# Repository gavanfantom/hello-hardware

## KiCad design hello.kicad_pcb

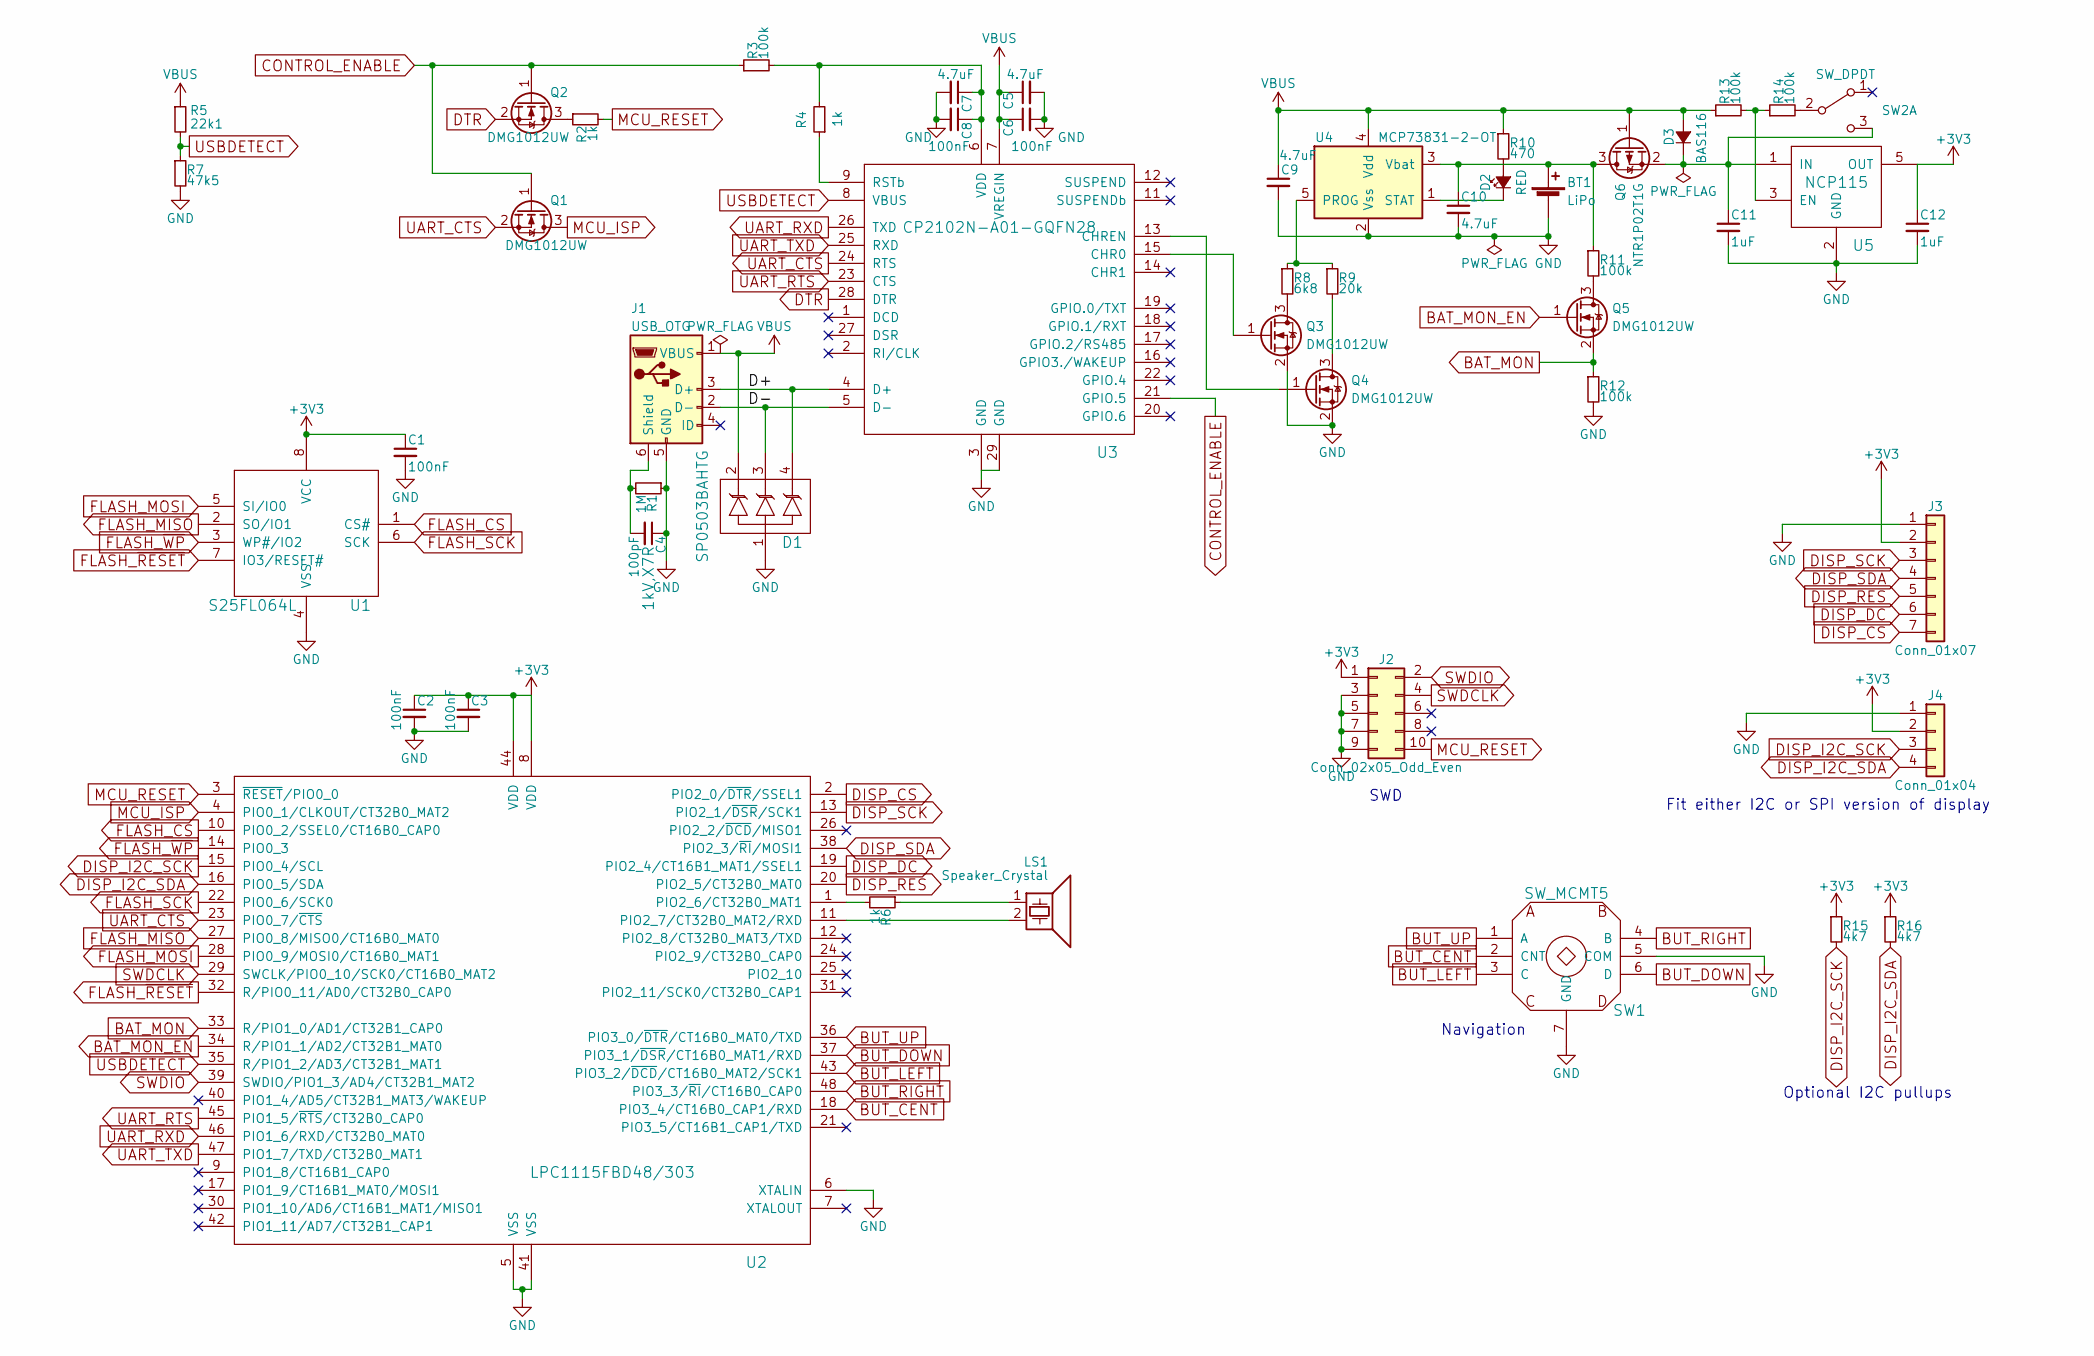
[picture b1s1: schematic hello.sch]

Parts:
BT1: LiPo; JST_PH_S2B-PH-SM4-TB_02x2.00mm_Angled; MPN S2B-PH-SM4-TB(LF)(SN)
C1, C2, C3, C6, C8: 100nF; C_0402; MPN MC0402B104K160CT
C4: 100pF; C_0805; MPN 885342207015
C5, C7, C9, C10: 4.7uF; C_0402; MPN AMK105BJ475MV-F
C11, C12: 1uF; C_0402; MPN GRM155R61E105KA12D
D1: SP0503BAHTG; SOT-143; MPN SP0503BAHTG
D2: RED; LED_0603; MPN KPT-1608EC
D3: BAS116; SOT-23; MPN BAS116 RF
J1: USB_OTG; USB_Micro-B_10118193-0001LF; MPN 10118193-0001LF
J2: Conn_02x05_Odd_Even; Pin_Header_Straight_2x05_Pitch1.27mm
J3: Conn_01x07; Pin_Header_Straight_1x07_Pitch2.54mm
J4: Conn_01x04; Pin_Header_Straight_1x04_Pitch2.54mm
LS1: Speaker_Crystal; PKMCS0909E4000-R1; MPN PKMCS0909E4000-R1
Q1, Q2, Q3, Q4, Q5: DMG1012UW; SOT-323_SC-70; MPN DMG1012UW
Q6: NTR1P02T1G; SOT-23; MPN NTR1P02T1G
R1: 1M; R_0603; MPN MCWR06X1004FTL
R2, R4, R6: 1k; R_0402; MPN MCWR04X1001FTL
R3, R11, R12, R13, R14: 100k; R_0402; MPN ERJ2RKF1003X
R5: 22k1; R_0402; MPN MCWR04X2212FTL
R7: 47k5; R_0402; MPN MCWR04X4752FTL
R8: 6k8; R_0402; MPN MCWR04X6801FTL
R9: 20k; R_0402; MPN MCWR04X2002FTL
R10: 470; R_0402; MPN MCWR04X4700FTL
R15, R16: 4k7; R_0402; MPN MCWR04X4701FTL
SW1: SW_MCMT5; Multicomp_MCMT5; MPN MCMT5-F-V
SW2: SW_DPDT; CK_JS202011SCQN; MPN JS202011SCQN
U1: S25FL064L; SOIJ-8_5.3x5.3mm_Pitch1.27mm; MPN S25FL064LABMFI010
U2: LPC1115FBD48/303; LQFP-48_7x7mm_Pitch0.5mm; MPN LPC1115FBD48/303
U3: CP2102N-A01-GQFN28; QFN-28-1EP_5x5mm_Pitch0.5mm; MPN CP2102N-A01-GQFN28
U4: MCP73831-2-OT; SOT-23-5; MPN MCP73831T-2ACI/OT
U5: NCP115; TSOP-5; MPN NCP115ASN330T2G

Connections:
+3V3: C1.1, C2.1, C3.1, C12.1, J2.1, J3.2, J4.2, R15.1, R16.1, U1.8 (VCC), U2.8 (VDD), U2.44 (VDD), U5.5 (OUT)
/D+: D1.4, J1.3 (D+), U3.4 (D+)
/D-: D1.3, J1.2 (D-), U3.5 (D-)
BAT_MON: Q5.2 (S), R12.1, U2.33 (R/PIO1_0/AD1/CT32B1_CAP0)
BAT_MON_EN: Q5.1 (G), U2.34 (R/PIO1_1/AD2/CT32B1_MAT0)
BUT_CENT: SW1.2 (CNT), U2.18 (PIO3_4/CT16B0_CAP1/RXD)
BUT_DOWN: SW1.6 (D), U2.37 (PIO3_1/~DSR~/CT16B0_MAT1/RXD)
BUT_LEFT: SW1.3 (C), U2.43 (PIO3_2/~DCD~/CT16B0_MAT2/SCK1)
BUT_RIGHT: SW1.4 (B), U2.48 (PIO3_3/~RI~/CT16B0_CAP0)
BUT_UP: SW1.1 (A), U2.36 (PIO3_0/~DTR~/CT16B0_MAT0/TXD)
CONTROL_ENABLE: Q1.1 (G), Q2.1 (G), R3.1, U3.21 (GPIO.5)
DISP_CS: J3.7, U2.2 (PIO2_0/~DTR~/SSEL1)
DISP_DC: J3.6, U2.19 (PIO2_4/CT16B1_MAT1/SSEL1)
DISP_I2C_SCK: J4.3, R15.2, U2.15 (PIO0_4/SCL)
DISP_I2C_SDA: J4.4, R16.2, U2.16 (PIO0_5/SDA)
DISP_RES: J3.5, U2.20 (PIO2_5/CT32B0_MAT0)
DISP_SCK: J3.3, U2.13 (PIO2_1/~DSR~/SCK1)
DISP_SDA: J3.4, U2.38 (PIO2_3/~RI~/MOSI1)
DTR: Q2.2 (S), U3.28 (DTR)
FLASH_CS: U1.1 (CS#), U2.10 (PIO0_2/SSEL0/CT16B0_CAP0)
FLASH_MISO: U1.2 (SO/IO1), U2.27 (PIO0_8/MISO0/CT16B0_MAT0)
FLASH_MOSI: U1.5 (SI/IO0), U2.28 (PIO0_9/MOSI0/CT16B0_MAT1)
FLASH_SCK: U1.6 (SCK), U2.22 (PIO0_6/SCK0)
FLASH_~RESET~: U1.7 (IO3/RESET#), U2.32 (R/PIO0_11/AD0/CT32B0_CAP0)
FLASH_~WP~: U1.3 (WP#/IO2), U2.14 (PIO0_3)
GND: BT1.2 (-), C1.2, C2.2, C3.2, C4.1, C5.2, C6.2, C7.2, C8.2, C9.2, C10.2, C11.2, C12.2, D1.1, J1.5 (GND), J2.3, J2.5, J2.7, J2.9, J3.1, J4.1, Q3.2 (S), Q4.2 (S), R1.1, R7.2, R12.2, SW1.5 (COM), SW1.7 (GND), U1.4 (VSS), U2.5 (VSS), U2.6 (XTALIN), U2.41 (VSS), U3.3 (GND), U3.29 (GND), U4.2 (Vss), U5.2 (GND)
MCU_ISP: Q1.3 (D), U2.4 (PIO0_1/CLKOUT/CT32B0_MAT2)
MCU_RESET: J2.10, R2.2, U2.3 (~RESET~/PIO0_0)
unnamed: BT1.1 (+), C10.1, Q6.3 (D), R11.1, U4.3 (Vbat)
unnamed: C4.2, J1.6 (Shield), R1.2
unnamed: C7.1, C8.1, R3.2, R4.2, U3.6 (VDD)
unnamed: C11.1, D3.3 (K), Q6.2 (S), SW2.3 (C), U5.1 (IN)
unnamed: D2.1 (K), U4.1 (STAT)
unnamed: D2.2 (A), R10.2
unnamed: LS1.1, R6.1
unnamed: LS1.2, U2.11 (PIO2_7/CT32B0_MAT2/RXD)
unnamed: Q2.3 (D), R2.1
unnamed: Q3.1 (G), U3.15 (CHR0)
unnamed: Q3.3 (D), R8.2
unnamed: Q4.1 (G), U3.13 (CHREN)
unnamed: Q4.3 (D), R9.2
unnamed: Q5.3 (D), R11.2
unnamed: R4.1, U3.9 (RSTb)
unnamed: R6.2, U2.1 (PIO2_6/CT32B0_MAT1)
unnamed: R8.1, R9.1, U4.5 (PROG)
unnamed: R13.2, R14.1, U5.3 (EN)
unnamed: R14.2, SW2.2 (B)
SWDCLK: J2.4, U2.29 (SWCLK/PIO0_10/SCK0/CT16B0_MAT2)
SWDIO: J2.2, U2.39 (SWDIO/PIO1_3/AD4/CT32B1_MAT2)
UART_CTS: Q1.2 (S), U2.23 (PIO0_7/~CTS~), U3.24 (RTS)
UART_RTS: U2.45 (PIO1_5/~RTS~/CT32B0_CAP0), U3.23 (CTS)
UART_RXD: U2.46 (PIO1_6/RXD/CT32B0_MAT0), U3.26 (TXD)
UART_TXD: U2.47 (PIO1_7/TXD/CT32B0_MAT1), U3.25 (RXD)
USBDETECT: R5.2, R7.1, U2.35 (R/PIO1_2/AD3/CT32B1_MAT1), U3.8 (VBUS)
VBUS: C5.1, C6.1, C9.1, D1.2, D3.1 (A), J1.1 (VBUS), Q6.1 (G), R5.1, R10.1, R13.1, U3.7 (VREGIN), U4.4 (Vdd)

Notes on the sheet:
Optional I2C pullups
Fit either I2C or SPI version of display
SWD
Navigation

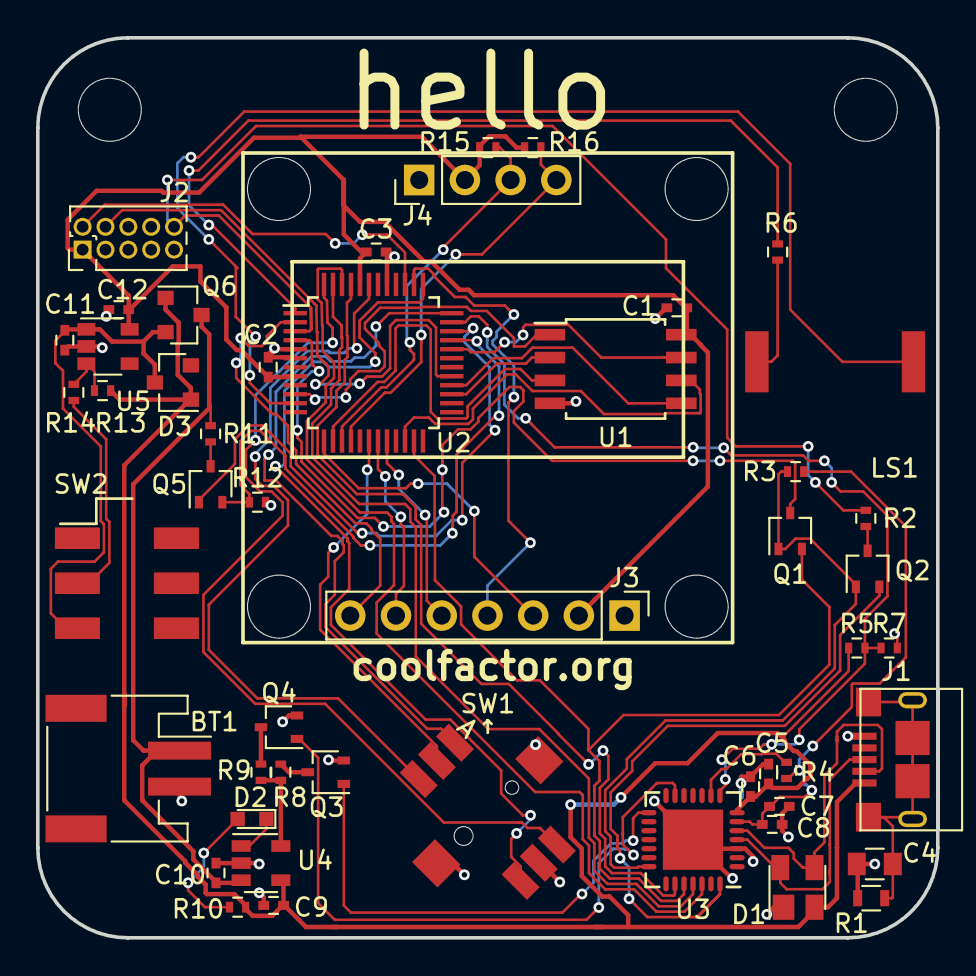
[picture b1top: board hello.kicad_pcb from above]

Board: 2 copper layers, 50.0 x 50.0 mm, 50 parts (0 on the bottom side), 55 nets.

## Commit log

2019-06-19 Initial tweaks to licence and readme
2019-06-19 Don't ignore KiCad cache files
2019-06-19 Initial commit of hello PCB version 1
2019-06-20 The mounting holes of the USB connector are 6.6mm apart, not 7mm.
2019-06-25 Fix pinout for BAS116 diode (D3)
2019-06-25 Update version number to 1b
